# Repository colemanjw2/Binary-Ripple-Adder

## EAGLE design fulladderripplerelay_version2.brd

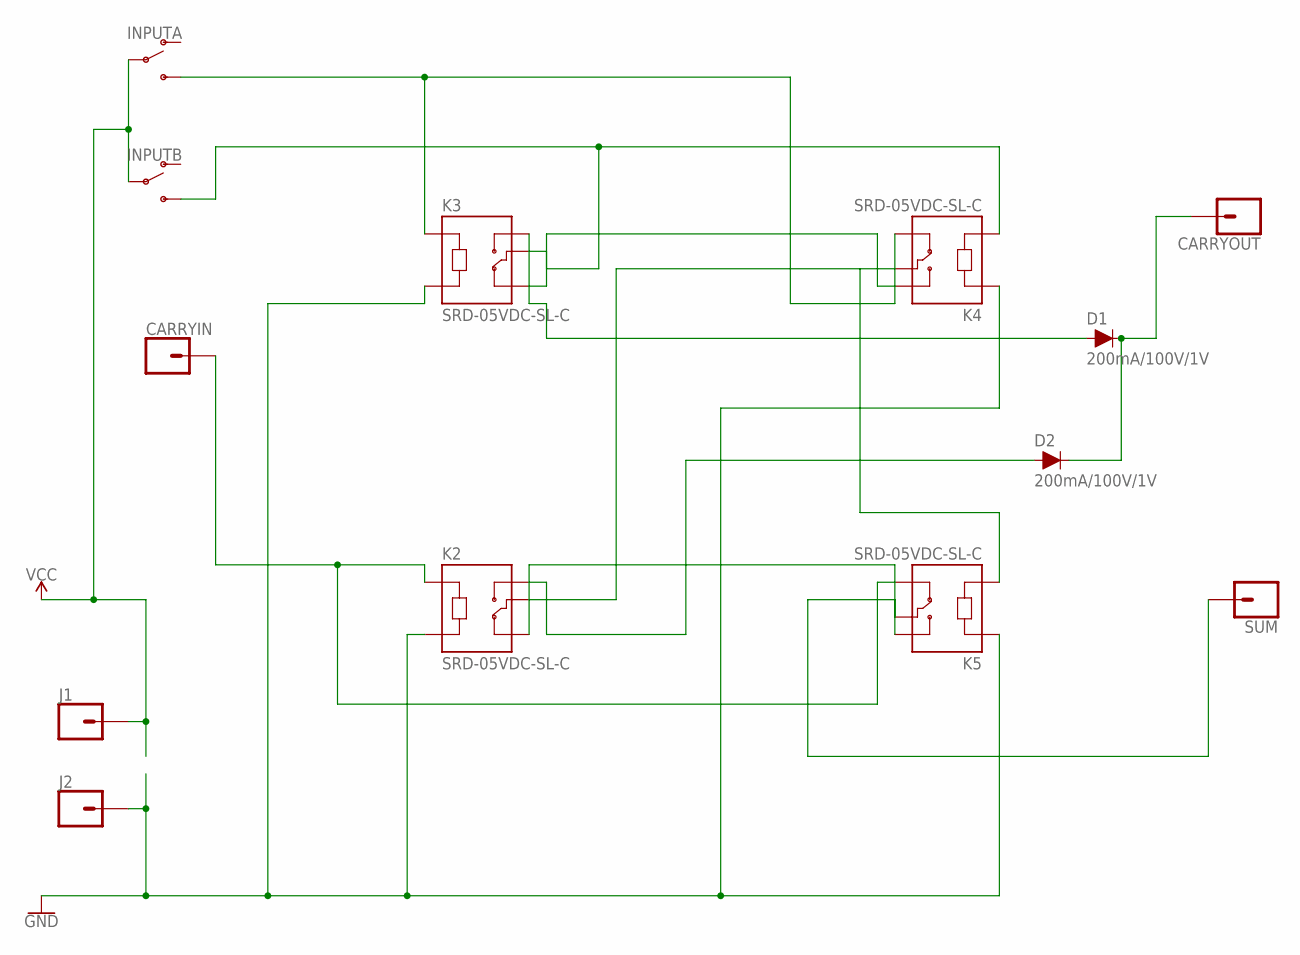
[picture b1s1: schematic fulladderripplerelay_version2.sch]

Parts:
CARRYIN: CONN_01PTH_LONGPAD; 1X01_LONGPAD
CARRYOUT: CONN_01PTH_LONGPAD; 1X01_LONGPAD
D1, D2: 200mA/100V/1V; DIODE-1N4148
INPUTA: SWITCH-SPDT-PTH-11.6X4.0MM; SWITCH_SPDT_PTH_11.6X4.0MM
INPUTB: SWITCH-SPDT-PTH-11.6X4.0MM; SWITCH_SPDT_PTH_11.6X4.0MM
J1, J2: CONN_01PTH_LONGPAD; 1X01_LONGPAD
K2, K3, K4, K5: SRD-05VDC-SL-C; RELAY_SRD-05VDC-SL-C
SUM: CONN_01PTH_LONGPAD; 1X01_LONGPAD

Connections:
GND: J2.1, K2.A2, K3.A2, K4.A1, K5.A1
unnamed: INPUTA.3 (S), K3.A1, K4.NC
unnamed: K3.NC, K4.NO
unnamed: D1.A, K3.NO
unnamed: CARRYOUT.1, D1.C, D2.C
unnamed: INPUTB.3 (S), K3.COM, K4.A2
unnamed: K2.COM, K4.COM, K5.A2
unnamed: K2.NC, K5.NO
unnamed: D2.A, K2.NO
unnamed: K5.COM, SUM.1
unnamed: CARRYIN.1, K2.A1, K5.NC
VCC: INPUTA.2, INPUTB.2, J1.1

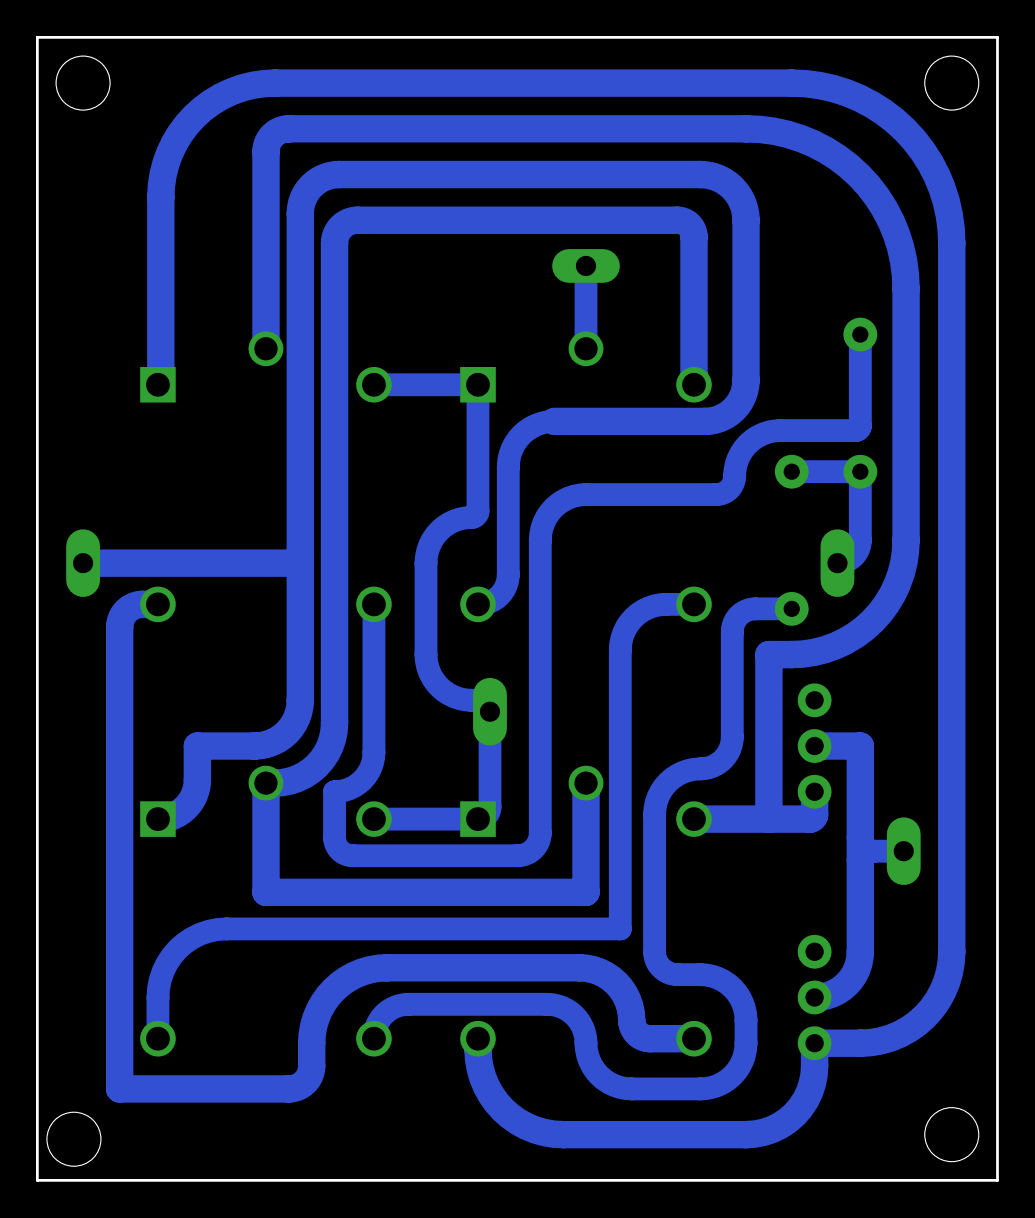
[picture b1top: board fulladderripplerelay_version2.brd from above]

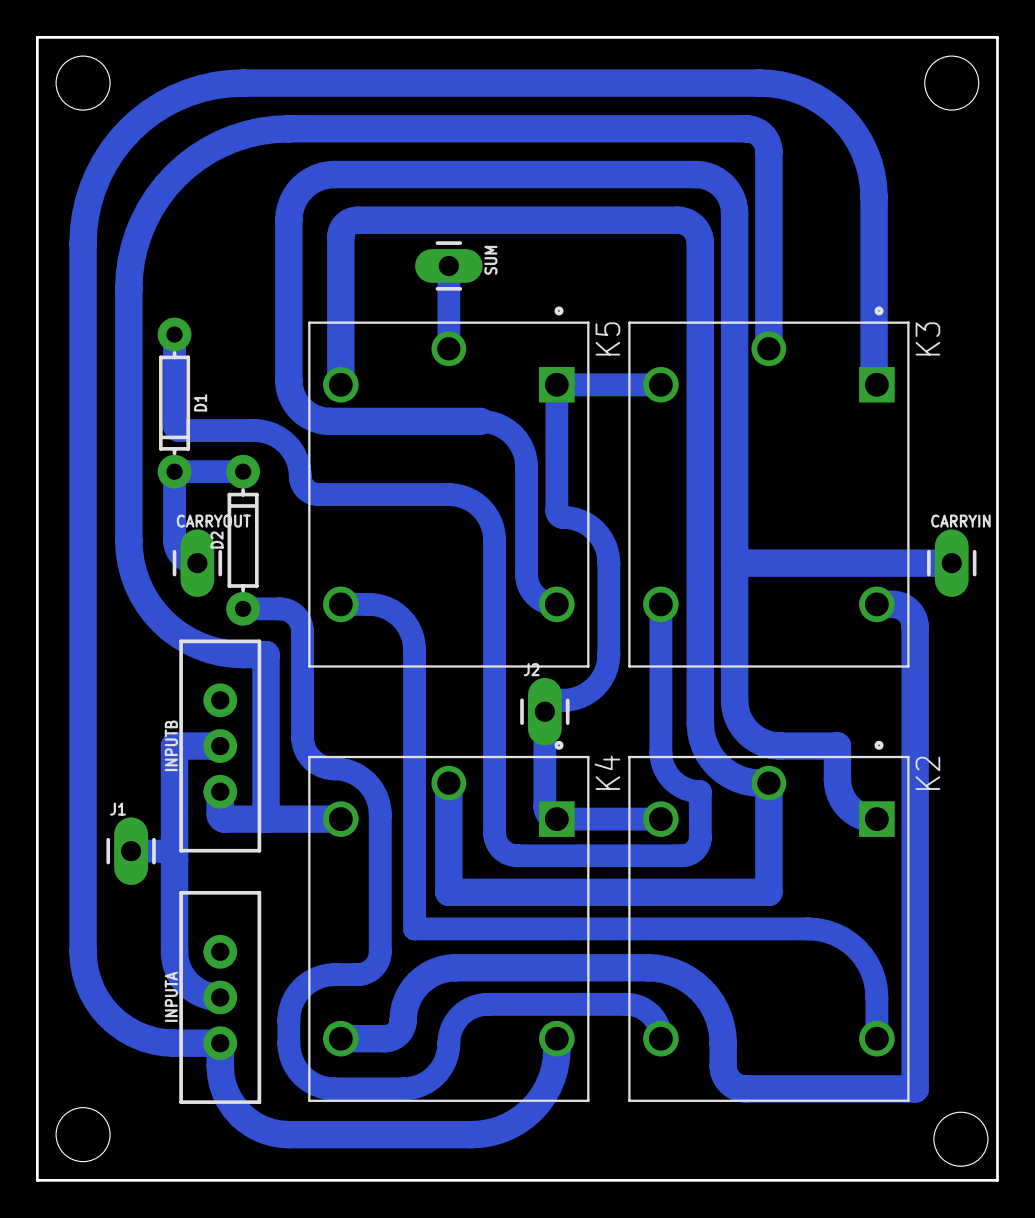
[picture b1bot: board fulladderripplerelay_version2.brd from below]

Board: 2 copper layers, 53.3 x 63.5 mm, 13 parts (13 on the bottom side), 12 nets.

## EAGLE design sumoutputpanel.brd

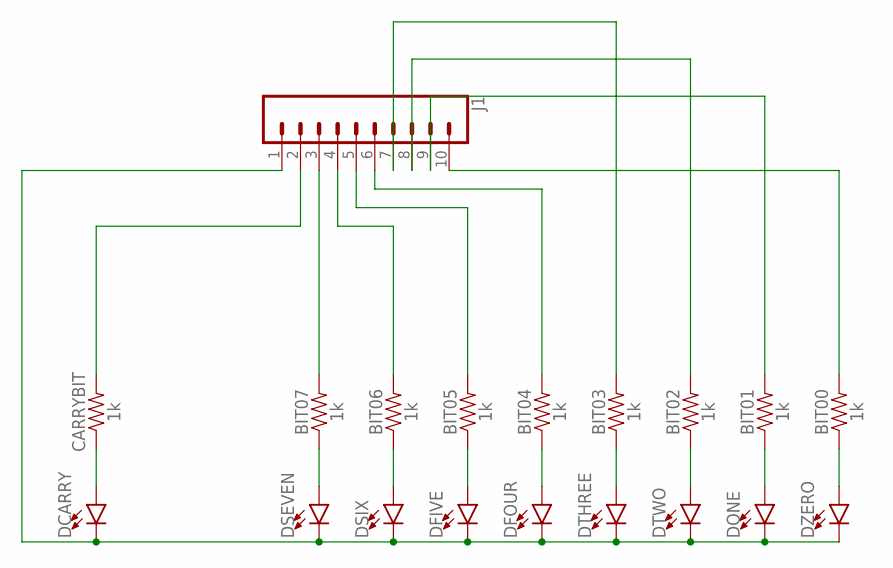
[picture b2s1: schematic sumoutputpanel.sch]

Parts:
BIT00, BIT01, BIT02, BIT03, BIT04, BIT05, BIT06, BIT07: 1k; AXIAL-0.3
CARRYBIT: 1k; AXIAL-0.3
DCARRY: LED5MM; LED_5MM
DFIVE: LED5MM; LED_5MM
DFOUR: LED5MM; LED_5MM
DONE: LED5MM; LED_5MM
DSEVEN: LED5MM; LED_5MM
DSIX: LED5MM; LED_5MM
DTHREE: LED5MM; LED_5MM
DTWO: LED5MM; LED_5MM
DZERO: LED5MM; LED_5MM
J1: CONN_10"; 1X10

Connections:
unnamed: CARRYBIT.P$2 (2), J1.2
unnamed: BIT07.P$2 (2), J1.3
unnamed: BIT06.P$2 (2), J1.4
unnamed: BIT05.P$2 (2), J1.5
unnamed: BIT04.P$2 (2), J1.6
unnamed: BIT03.P$2 (2), J1.7
unnamed: BIT02.P$2 (2), J1.8
unnamed: BIT01.P$2 (2), J1.9
unnamed: BIT00.P$2 (2), J1.10
unnamed: CARRYBIT.P$1 (1), DCARRY.A
unnamed: BIT07.P$1 (1), DSEVEN.A
unnamed: BIT06.P$1 (1), DSIX.A
unnamed: BIT05.P$1 (1), DFIVE.A
unnamed: BIT04.P$1 (1), DFOUR.A
unnamed: BIT03.P$1 (1), DTHREE.A
unnamed: BIT02.P$1 (1), DTWO.A
unnamed: BIT01.P$1 (1), DONE.A
unnamed: BIT00.P$1 (1), DZERO.A
unnamed: DCARRY.K (C), DFIVE.K (C), DFOUR.K (C), DONE.K (C), DSEVEN.K (C), DSIX.K (C), DTHREE.K (C), DTWO.K (C), DZERO.K (C), J1.1

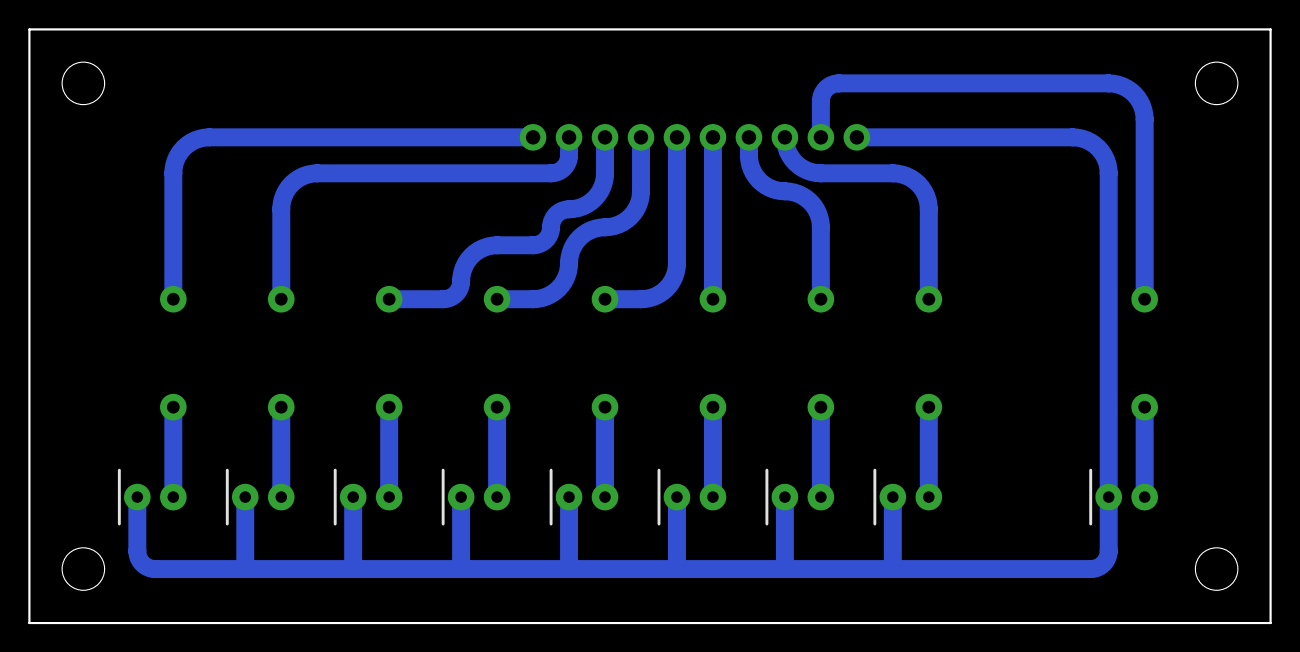
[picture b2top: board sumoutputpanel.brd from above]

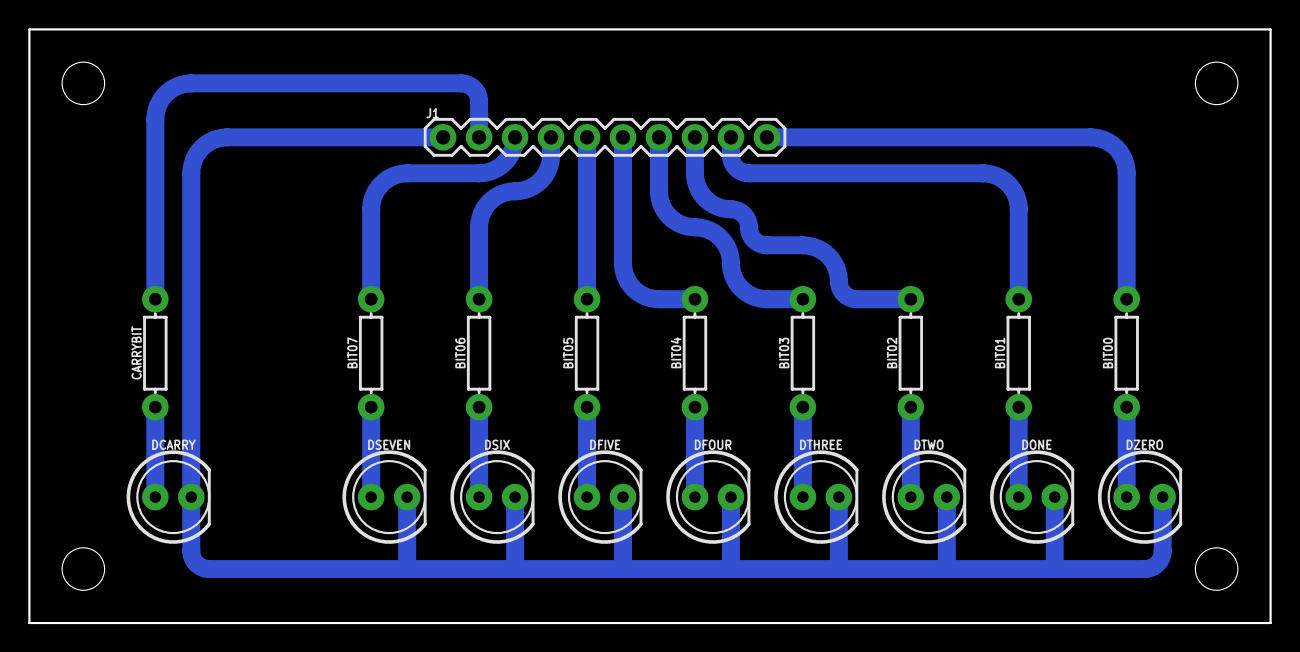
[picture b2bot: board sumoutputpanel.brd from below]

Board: 2 copper layers, 87.6 x 41.9 mm, 19 parts (19 on the bottom side), 19 nets.

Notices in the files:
parts and their libraries:
SparkFun-Connectors: Licensing: Creative Commons ShareAlike 4.0 International - https://creativecommons.org/licenses/by-sa/4.0
